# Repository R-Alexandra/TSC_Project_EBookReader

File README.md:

# TSC_Project_EBookReader - Rădulescu Alexandra

Acest proiect reprezintă un sistem de tip **eBook Reader** bazat pe microcontrolerul **ESP32-C6**, ce integrează module de stocare, afișare, senzori de mediu, alimentare prin baterie și interfețe de conectivitate. Dispozitivul este proiectat pentru un consum energetic scăzut și este compatibil cu multiple tipuri de afișaje E-Ink.

---
## Diagramă Bloc

---

## Bill of Materials (BOM)

| Componentă                | Link Achiziționare | Link Datasheet |
|---------------------------|--------------------|----------------|
| 112A-TAAR-R03 ATTEND      | https://store.comet.srl.ro/Catalogue/Product/43497/ | https://www.snapeda.com/parts/112A-TAAR-R03/Attend/datasheet/ |
| Condensator C0402         | https://ro.mouser.com/c/passive-components/capacitors/ceramic-capacitors/?q=CC0402 | https://componentsearchengine.com/Datasheets/2/CC0402MRX5R5BB106.pdf |
| Condensator Tantalum      | https://ro.mouser.com/ProductDetail/KYOCERA-AVX/TAJW107M010RNJ?qs=Wtp%252Bf%2FAeVqIH8v1VxV%252B1Rg%3D%3D | https://ro.mouser.com/datasheet/2/40/TAJ-3165264.pdf |
| CHG_LED                   | https://ro.mouser.com/ProductDetail/Kingbright/KP-1608SURCK?qs=2JU0tDl2GZ3FuyEWfBV1%2Fg== | https://www.snapeda.com/parts/KP-1608SURCK/Kingbright/datasheet/ |
| USBLC6-2SC6Y              | https://ro.mouser.com/ProductDetail/STMicroelectronics/USBLC6-2SC6Y?qs=gNDSiZmRJS%2FOgDexvXkdow%3D%3D | https://ro.mouser.com/datasheet/2/389/usblc6_2sc6y-1852505.pdf |
| SD0805S020S1R0            | https://ro.mouser.com/ProductDetail/KYOCERA-AVX/SD0805S020S1R0?qs=jCA%252BPfw4LHbpkAoSnwrdjw%3D%3D | https://ro.mouser.com/datasheet/2/40/schottky-3165252.pdf |
| MBR0530                   | https://ro.mouser.com/ProductDetail/onsemi-Fairchild/MBR0530?qs=VOMQJJE%252BBNniwJKcE3T43Q== | https://ro.mouser.com/datasheet/2/308/MBR0530_D-1810985.pdf |
| PGB1010603MR              | https://www.digikey.com/en/products/detail/littelfuse-inc/PGB1010603MR/715755 | https://www.littelfuse.com/assetdocs/pulseguard-esd-suppressors-pgb1-datasheet?assetguid=8a337998-d54d-466b-be4e-dc5bcd1f9321 |
| Rezistență R0402         | https://ro.mouser.com/c/passive-components/resistors/smd-resistors-chip-resistors/?case%20code%20-%20in=0402 | https://www.yageo.com/upload/media/product/products/datasheet/rchip/PYu-RC_Group_51_RoHS_L_12.pdf |
| BME680                    | https://ro.mouser.com/ProductDetail/Bosch-Sensortec/BME688?qs=IS%252B4QmGtzzqQoVDscqwx3A%3D%3D | https://ro.mouser.com/datasheet/2/783/bst_bme688_fl000-2307034.pdf |
| W25Q512JVEIQ              | https://ro.mouser.com/ProductDetail/Winbond/W25Q512JVEIQ?qs=l7cgNqFNU1jw6svr3at6tA%3D%3D | https://ro.mouser.com/datasheet/2/949/Winbond_W25Q512JV_Datasheet-3240039.pdf |
| ESP32-C6-WROOM-1-N8       | https://ro.mouser.com/ProductDetail/Espressif-Systems/ESP32-C6-WROOM-1-N8?qs=8Wlm6%252BaMh8ST02Gmwp74cw%3D%3D | https://ro.mouser.com/datasheet/2/891/Espressif_ESP32_C6_WROOM_1__Datasheet_V0_1_PRELIMI-3239987.pdf |
| DS3231SN#                 | https://ro.mouser.com/ProductDetail/Analog-Devices-Maxim-Integrated/DS3231SN?qs=1eQvB6Dk1vhUlr8%2FOrV0Fw%3D%3D | https://ro.mouser.com/datasheet/2/609/DS3231-3421123.pdf |
| MAX17048G+T10             | https://ro.mouser.com/ProductDetail/Analog-Devices-Maxim-Integrated/MAX17048G%2bT10?qs=D7PJwyCwLAoGnnn8jEPRBQ%3D%3D | https://ro.mouser.com/datasheet/2/609/MAX17048_MAX17049-3469099.pdf |
| MCP73831                  | https://ro.mouser.com/ProductDetail/Microchip-Technology/MCP73831T-2ATI-OT?qs=yUQqVecv4qsZbioEUu%252B83g%3D%3D | https://ro.mouser.com/datasheet/2/268/MCP73831_Family_Data_Sheet_DS20001984H-3441711.pdf |
| BD5229G-TR                | https://www.digikey.com/en/products/detail/rohm-semiconductor/BD5229G-TR/3663792 | https://fscdn.rohm.com/en/products/databook/datasheet/ic/power/voltage_detector/bd52xxg-e.pdf |
| XC6220A331MR-G            | https://ro.mouser.com/ProductDetail/Torex-Semiconductor/XC6220A331MR-G?qs=AsjdqWjXhJ8ZSWznL1J0gg%3D%3D | https://ro.mouser.com/datasheet/2/760/xc6220-3371556.pdf |
| FH34SRJ-24S-0.5SH(99)     | https://ro.mouser.com/ProductDetail/Hirose-Connector/FH34SRJ-24S-0.5SH99?qs=vcbW%252B4%252BSTIpKBl5ap9J8Fw%3D%3D | https://ro.mouser.com/datasheet/2/185/FH34SRJ_24S_0_5SH_99__CL0580_1255_6_99_2DDrawing_0-1615044.pdf |
| USB4110-GF-A              | https://ro.mouser.com/ProductDetail/GCT/USB4110-GF-A?qs=KUoIvG%2F9IlYiZvIXQjyJeA%3D%3D | https://ro.mouser.com/datasheet/2/837/GCT_USB4110_Product_Drawing___20k_cycles-3455479.pdf |
| QWIIC_RIGHT_ANGLE         | https://ro.mouser.com/ProductDetail/SparkFun/PRT-14417?qs=wd5RIQLrsJhgdz%2FpmZ%2F3GQ== | https://ro.mouser.com/datasheet/2/813/Qwiic_Connector_Datasheet-1223982.pdf |
| Bobină 744043680         | https://ro.mouser.com/ProductDetail/Wurth-Elektronik/744043680?qs=PGXP4M47uW6VkZq%252BkzjrHA%3D%3D | https://www.we-online.com/components/products/datasheet/744043680.pdf |
| PFMF.050.1                | https://ro.mouser.com/ProductDetail/EPCOS-TDK/B72520T0350K062?qs=dEfas%2FXlABIszF52uu7vrg%3D%3D | https://www.tdk-electronics.tdk.com/inf/75/db/CTVS_14/Surge_protection_series.pdf |
| DMG2305UX-7               | https://www.digikey.com/en/products/detail/diodes-incorporated/DMG2305UX-7/4340666 | https://www.diodes.com/assets/Datasheets/DMG2305UX.pdf |
| Si1308EDL-T1-GE3          | https://www.digikey.com/en/products/detail/vishay-siliconix/SI1308EDL-T1-GE3/4876435 | https://www.vishay.com/docs/63399/si1308edl.pdf |
| Solder Jumper (SJ)        | https://grabcad.com/library/solder-jumpers-1 | https://grabcad.com/library/solder-jumpers-1 |
| Buton                     | https://industry.panasonic.com/global/en/products/control/switch/light-touch/number/evqpuj02k | https://industry.panasonic.com/global/en/downloads?tab=catalog&small_g_cd=203&part_no=EVQPUJ02K |
| CPH3225A                  | https://www.digikey.com/en/products/detail/seiko-instruments/CPH3225A/8692444 | https://mm.digikey.com/Volume0/opasdata/d220001/medias/docus/6537/rev05-CPHCPM.pdf |

---

## Descriere a componentelor și funcționalității hardware

### Microcontroller: ESP32-C6

- Microcontroller RISC-V pe 32 de biți cu suport **Wi-Fi 6** și **Bluetooth 5 Low Energy (BLE)**
- Alimentat la **3.3V**
- Gestionează toate perifericele proiectului
- Oferă multiple interfețe  **GPIO, SPI, I2C, UART**
  - **SPI**(Serial Peripheral Interface): pentru conectare la memoria NOR Flash, cardul SD și afișajul E-Ink
  - **I2C**(Inter-Integrated Circuit): pentru conectare la senzorul BME688, modulul RTC DS3231 și senzorul de nivel baterie MAX17048
  - **GPIO**(General Purpose Input/Output): utilizat pentru semnale de control pentru ecranul E-Ink, butoane și detecție SD
- Are o arhitectură optimizată pentru **consum redus de energie**, ideală pentru aplicații portabile

### Alimentare și protecție

#### Regulator de tensiune LDO

- **XC6206P332MR-G** transformă tensiunea VIN (5V) în 3.3V și  este folosit un tranzistor suplimentar pentru controlul alimentării

#### Controller de încărcare baterie

- **MCP73831** gestionează încărcarea bateriei Li-Po 3.7V cu protecție integrată contra supratensiunii și a curentului excesiv
- LED-uri pentru semnalizare stare de încărcare

#### Monitorizare nivel baterie

- **MAX17048** oferă monitorizare în timp real a stării de încărcare a bateriei 
- Comunică cu ESP32-C6 prin interfața I2C

#### Conector USB-C și protecție ESD

- Conector **USB-C** pentru alimentare și comunicație
- Protecție la descărcări electrostatice realizată prin **PMF0501** și **USBLC6-2SC6Y**, care protejează liniile de alimentare și semnal

## Stocare

### Card microSD

- Conectat la magistrala **SPI**
- Permite stocarea fișierelor eBook și a jurnalelor de sistem
- Linie dedicată pentru **detectare automată** a cardului

### Memorie NOR Flash externă (64MB)

- Chipul **W25Q512JVEIQ** furnizeză memorie nevolatilă pentru firmware și resurse statice
- Conectată la magistrala **SPI**

## Afișaj E-Paper

### Interfață EPD dedicată

- Include toate conexiunile necesare pentru controlul unui ecran E-Ink (**SPI**, semnale de control precum **EPD_BUSY, EPD_DC, EPD_RST** etc).
- Header dedicat EPD cu 20 pini, compatibil cu mai multe modele DE afișaje.

### Circuit de alimentare EPD

- Utilizează un convertor DC-DC și tranzistoare MOSFET pentru a genera tensiunile de alimentare cerute de ecranele E-Ink.

### Selector tip afișaj

- Permite alegerea tipului de ecran conectat, în funcție de compatibilitatea cu semnalele de control.

## Senzor BME680

- Măsoară: **temperatură, umiditate, presiune atmosferică, calitate aer (VOCs)**
- Este conectat prin interfața **I2C** (SDA și SCL)

## Modul RTC (DS3231SN)

- Precizie ridicată pentru a păstra ora și data corectă, chiar și în absența alimentării principale.
- Interfață **I2C** (SDA și SCL)

## Butoane de control

- Buton **RESET**
- Buton **BOOT**
- Buton custom **IO/CHANGE**

## Test Pads și Conectori de extensie

- Sunt prezente **paduri de testare** și debugging 
- Conector **Qwiic/Stemma QT** pentru extinderea rapidă a sistemului cu senzori I2C suplimentari

## Protecție ESD pentru SPI

- Liniile **SPI** sunt protejate împotriva descărcărilor electrostatice

---

## Consum estimativ de energie
Sistemul este proiectat pentru un consum energetic redus, aspect esențial pentru funcționarea pe baterie.

| Componentă               | Consum estimativ       |
|--------------------------|-------------------------|
| ESP32-C6 (Wi-Fi activ)   | 120 – 150 mA            |
| Afișaj EPD               | 20 – 40 mA              |
| Senzor BME688            | 1 – 2 mA                |
| Card SD (scriere/citire)| 50 – 100 mA             |
| MAX17048 + RTC DS3231    | < 1 mA                  |
| **Total (mod activ)**    | **~300 mA**             |
| **Total (deep sleep)**   | **< 10 mA**             |

### Estimare autonomie (baterie LiPo 2000mAh):
- **Folosire intensivă**: câteva ore
- **Standby cu afiș static**: zile/săptămâni

---

## Alocarea pinilor ESP32-C6

### 1. Afișaj EPD (e-paper display)

| Pin ESP32-C6 | Funcție     | Observație                          |
|--------------|-------------|--------------------------------------|
| IO3 (26)     | EPD_BUSY    | Verifică dacă ecranul este ocupat   |
| IO5 (5)      | EPD_DC      | Comută între date și comandă        |
| IO6 (6)      | SCK         | Linie de ceas SPI                   |
| IO7 (7)      | MOSI        | Transmisie date SPI                 |
| IO10 (11)    | EPD_CS      | Selectare chip pentru EPD           |
| IO23 (21)    | EPD_RST     | Resetare ecran                      |
| IO20 (18)    | EPD_3V3_C   | Control alimentare 3V3 pentru EPD   |

### 2. Card SD

| Pin ESP32-C6 | Funcție     | Observație                          |
|--------------|-------------|--------------------------------------|
| IO2 (27)     | MISO        | Recepție date SPI                   |
| IO4 (4)      | SS_SD       | Selectare chip SD                   |
| IO6 (6)      | SCK         | Linie de ceas SPI                   |
| IO7 (7)      | MOSI        | Transmisie date SPI                 |

### 3. Memorie Flash NOR

| Pin ESP32-C6 | Funcție     | Observație                          |
|--------------|-------------|--------------------------------------|
| IO11 (12)    | FLASH_CS    | Selectare chip Flash                |
| IO2 (27)     | MISO        | Recepție date SPI                   |
| IO6 (6)      | SCK         | Linie de ceas SPI                   |
| IO7 (7)      | MOSI        | Transmisie date SPI                 |

### 4. Magistrală I2C (BME688, RTC DS3231, MAX17048)

| Pin ESP32-C6 | Funcție     | Observație                          |
|--------------|-------------|--------------------------------------|
| IO21 (19)    | SDA         | Linie de date I2C                   |
| IO22 (20)    | SCL         | Linie de ceas I2C                   |
| IO19 (17)    | I2C_PW      | Activare alimentare senzori I2C     |

### 5. RTC (DS3231)

| Pin ESP32-C6 | Funcție     | Observație                          |
|--------------|-------------|--------------------------------------|
| IO0 (8)      | INT_RTC     | Semnal de întrerupere               |
| IO1 (9)      | 32KHz       | Ieșire ceas precis                  |
| IO18 (16)    | RTC_RST     | Reset hardware RTC                  |

### 6. Conectivitate USB

| Pin ESP32-C6 | Funcție     | Observație                          |
|--------------|-------------|--------------------------------------|
| IO12 (13)    | USB_D-      | Comunicație USB                     |
| IO13 (14)    | USB_D+      | Comunicație USB                     |

### 7. Serială UART 

| Pin ESP32-C6 | Funcție     | Observație                          |
|--------------|-------------|--------------------------------------|
| IO16 (25)    | TX          | Transmisie UART                     |
| IO17 (24)    | RX          | Recepție UART                       |

### 8. Butoane 

| Pin ESP32-C6 | Funcție     | Observație                          |
|--------------|-------------|--------------------------------------|
| EN (3)       | RESET       | Reset general microcontroler        |
| IO8 (10)     | IO/BOOT     | Buton BOOT (pus pe GND la pornire)  |
| IO15 (23)    | IO/CHANGE   | Buton custom                        |

### 9. Alimentare și Referință

| Pin ESP32-C6 | Funcție     | Observație                          |
|--------------|-------------|--------------------------------------|
| Pin 2        | 3V3         | Alimentare principală               |
| Pin 1        | GND         | Împământare                         |

---

## Considerații privind realizarea proiectului
În procesul de realizare a designului hardware am respectat cerințele din ghidurile de proiectare (ERC, DRC, layout) și am încercat să iau decizii care să ofere echilibru între funcționalitate, integrare și respectarea bunelor practici. Amplasarea componentelor am făcut-o atât pe baza documentației oferite (dimensiuni mecanice și recomandări de placement), cât și pentru o rutare cât mai bună, care să reducă interferențele și să faciliteze traseele de alimentare și semnal.

Pentru designul PCB-ului, am folosit DRC-ul oferit pentru verificare și am rezolvat erorile apărute, inclusiv prin ajustarea dimensiunii unor footprint-uri. Am aplicat regulile de rutare pentru traseele de putere și pentru date, evitând unghiurile drepte. Traseele de alimentare au lățimea de 0.3mm, restul traseelor de 0.15mm și am realizat câte un plan de masă atât pentru top cât și pe bottom. Test pad-urile rămase le-am poziționat astfel încât să putem testa rapid anumite componente: 
- lângă header-ul display-ului pentru a testa alimentarea și semnalele de date către ecran;
- lângă ESP32-C6 pentru a verifica semnale critice și pentru debugging.

Am avut în vedere și integrarea finală în ansamblul 3D al carcasei. De aceea, am poziționat conectorii astfel încât să fie accesibili din exterior, iar unele componente au fost ușor translatate pentru a obține o potrivire corectă și o funcționare bună a dispozitivului. De asemenea, am desenat bateria și ecranul folosind dimensiunile mecanice specificate pentru o integrare cât mai bună.

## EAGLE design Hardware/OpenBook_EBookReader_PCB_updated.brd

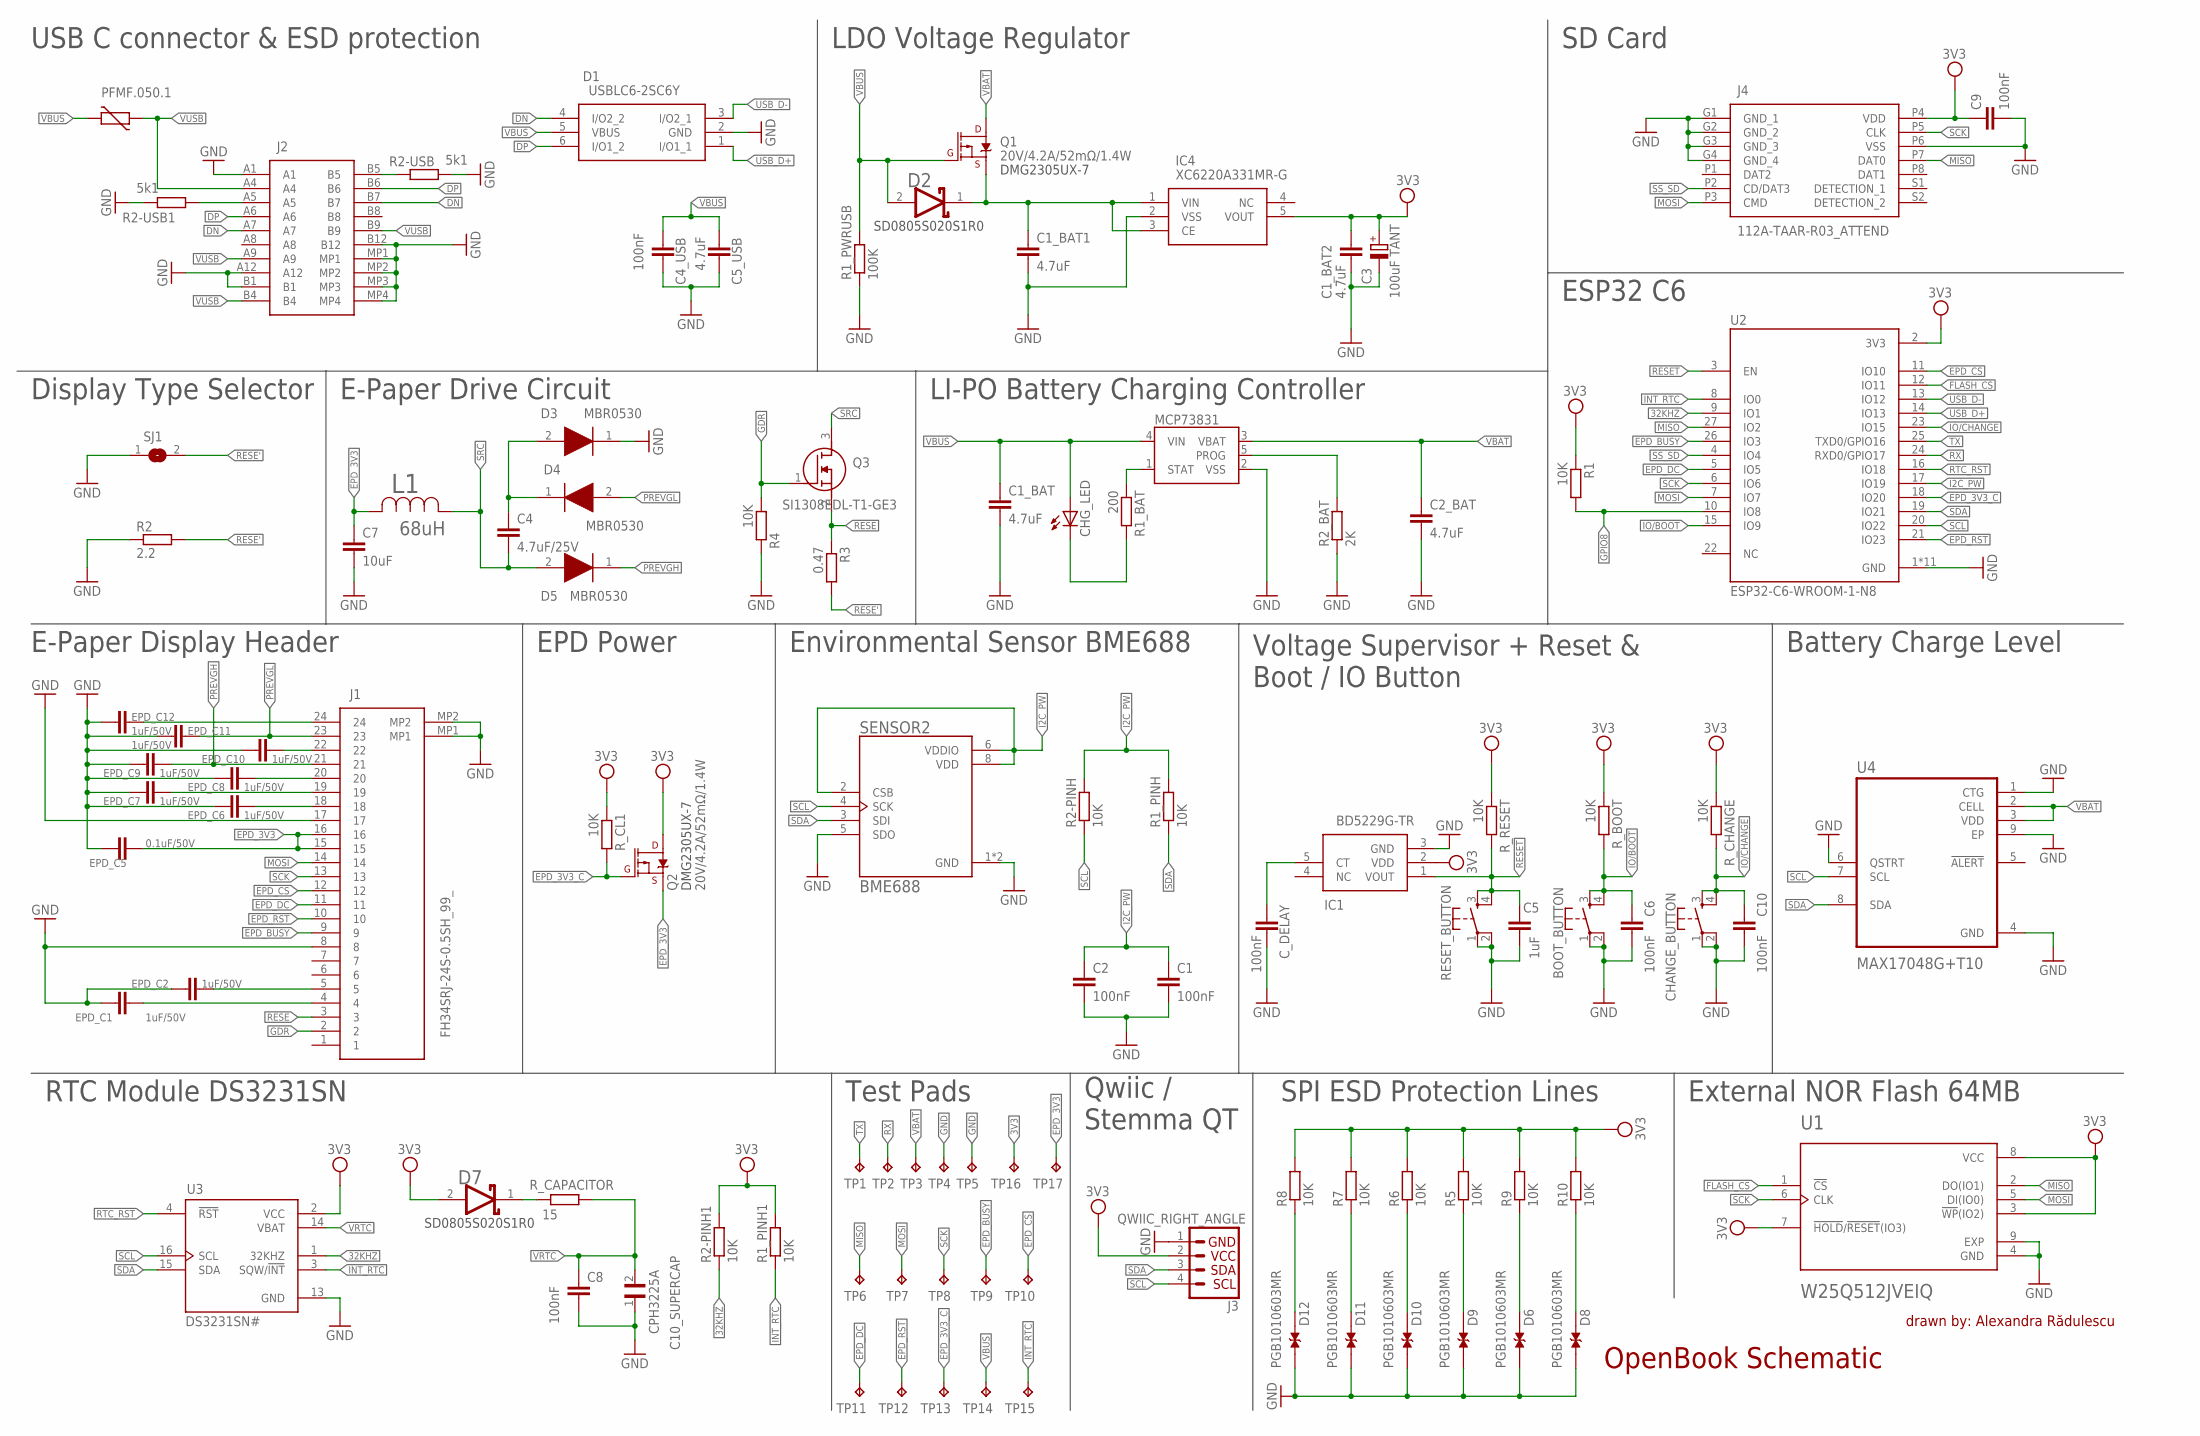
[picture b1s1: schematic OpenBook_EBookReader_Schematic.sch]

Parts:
BOOT_BUTTON: BUTTON_CUSYOMV1; MYBUTTON
C1, C2, C4_USB, C6, C8, C9, C10: 100nF; ESP32_WROVER_EAGLE-LTSPICE_C0402
C1_BAT, C1_BAT1, C1_BAT2, C2_BAT, C5_USB: 4.7uF; ESP32_WROVER_EAGLE-LTSPICE_C0402
C3: 100uF TANT; RCL_CT3528
C4: 4.7uF/25V; ESP32_WROVER_EAGLE-LTSPICE_C0402
C5: 1uF; ESP32_WROVER_EAGLE-LTSPICE_C0402
C7: 10uF; ESP32_WROVER_EAGLE-LTSPICE_C0402
C10_SUPERCAP: CPH3225A; CAPCP3225X100N
CHANGE_BUTTON: BUTTON_CUSYOMV1; MYBUTTON
CHG_LED: ADAFRUIT_LEDCHIP-LED0603; ADAFRUIT_CHIP-LED0603
C_DELAY: 100nF; ESP32_WROVER_EAGLE-LTSPICE_C0402
D1: USBLC6-2SC6Y; SOT95P280X145-6N
D2: ESP32_WROVER_AVX---SD0805S020S1R0_AVX_SD0805S020S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; ESP32_WROVER_AVX---SD0805S020S1R0_AVX_SD0805S020S1R0_0
D3, D4, D5: MBR0530; SOD3716X135N
D6, D8, D9, D10, D11, D12: PGB1010603MR; DIOC1608X36N
D7: SD0805S020S1R0; ESP32_WROVER_AVX---SD0805S020S1R0_AVX_SD0805S020S1R0_0
EPD_C1, EPD_C2, EPD_C6, EPD_C7, EPD_C8, EPD_C9, EPD_C10, EPD_C11, EPD_C12: 1uF/50V; ESP32_WROVER_EAGLE-LTSPICE_C0402
EPD_C5: 0.1uF/50V; ESP32_WROVER_EAGLE-LTSPICE_C0402
IC1: BD5229G-TR; SOT95P280X125-5N
IC4: XC6220A331MR-G; SOT95P280X120-5N
J1: FH34SRJ-24S-0.5SH_99_; FH34SRJ24S05SH99
J2: SAMACSYS_PARTS_USB4110-GF-A; SAMACSYS_PARTS_USB4110GFA
J3: QWIIC_RIGHT_ANGLE; JST04_1MM_RA
J4: 112A-TAAR-R03_ATTEND; 112ATAARR03ATTEND
L1: 68uH; IND_4828-WE-TPC_WRE
MCP73831: ESP32_WROVER_SPARKFUN-IC-POWER_MCP73831; ESP32_WROVER_SPARKFUN-IC-POWER_SOT23-5
PFMF.050.1: ESP32C6_VARISTORCN1812; ESP32C6_VARISTOR_CT/CN1812
Q1, Q2: 20V/4.2A/52mΩ/1.4W; ESP32_WROVER_SPARKFUN-DISCRETESEMI_SOT23-3
Q3: SI1308EDL-T1-GE3; SOT65P210X110-3N
R1, R1_PINH, R1_PINH1, R2-PINH, R2-PINH1, R4, R5, R6, R7, R8, R9, R10: 10K; ESP32_WROVER_EAGLE-LTSPICE_R0402
R1_BAT: 200; ESP32_WROVER_EAGLE-LTSPICE_R0402
R1_PWRUSB: 100K; ESP32_WROVER_EAGLE-LTSPICE_R0402
R2: 2.2; ESP32_WROVER_EAGLE-LTSPICE_R0402
R2-USB, R2-USB1: 5k1; ESP32_WROVER_EAGLE-LTSPICE_R0402
R2_BAT: 2K; ESP32_WROVER_EAGLE-LTSPICE_R0402
R3: 0.47; ESP32_WROVER_EAGLE-LTSPICE_R0402
RESET_BUTTON: BUTTON_CUSYOMV1; MYBUTTON
R_BOOT: 10K; ESP32_WROVER_EAGLE-LTSPICE_R0402
R_CAPACITOR: 15; ESP32_WROVER_EAGLE-LTSPICE_R0402
R_CHANGE: 10K; ESP32_WROVER_EAGLE-LTSPICE_R0402
R_CL1: 10K; ESP32_WROVER_EAGLE-LTSPICE_R0402
R_RESET: 10K; ESP32_WROVER_EAGLE-LTSPICE_R0402
SENSOR2: BME688; ESP32_WROVER_BME680_PSON80P300X300X100-8N
SJ1: SJ
TP1, TP2, TP3, TP4, TP5, TP6, TP7, TP8, TP9, TP10, TP11, TP12, TP13, TP14, TP15, TP16, TP17: TPTP20R; TP20R
U1: W25Q512JVEIQ; SON127P600X800X80-9N
U2: ESP32-C6-WROOM-1-N8; XCVR_ESP32-C6-WROOM-1-N8
U3: DS3231SN#; SOIC127P1032X265-16N
U4: MAX17048G+T10; SON50P200X200X80-9N

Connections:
3V3: C1_BAT2.1, C3.+, C9.1, D7.2 (ANODE), IC1.2 (VDD), IC4.5 (VOUT), J3.2, J4.P4 (VDD), Q2.3 (D), R1.1, R1_PINH1.2, R2-PINH1.2, R5.2, R6.2, R7.2, R8.2, R9.2, R10.2, R_BOOT.1, R_CHANGE.1, R_CL1.1, R_RESET.1, TP16.TP, U1.3 (!WP!(IO2)), U1.7 (!HOLD!/!RESET!(IO3)), U1.8 (VCC), U2.2 (3V3), U3.2 (VCC)
32KHZ: R2-PINH1.1, U2.9 (IO1), U3.1 (32KHZ)
DN: D1.4 (I/O2_2), J2.A7, J2.B7
DP: D1.6 (I/O1_2), J2.A6, J2.B6
EPD_3V3: C7.1, EPD_C5.1, J1.15, J1.16, L1.2, Q2.2 (S), TP17.TP
EPD_3V3_C: Q2.1 (G), R_CL1.2, TP13.TP, U2.18 (IO20)
EPD_BUSY: J1.9, TP9.TP, U2.26 (IO3)
EPD_CS: J1.12, TP10.TP, U2.11 (IO10)
EPD_DC: J1.11, TP11.TP, U2.5 (IO5)
EPD_RST: J1.10, TP12.TP, U2.21 (IO23)
FLASH_CS: U1.1 (!CS), U2.12 (IO11)
GDR: J1.2, Q3.1 (G), R4.1
GND: BOOT_BUTTON.1, BOOT_BUTTON.2, C1.2, C1_BAT.2, C1_BAT1.2, C1_BAT2.2, C2.2, C2_BAT.2, C3.-, C4_USB.2, C5.2, C5_USB.2, C6.2, C7.2, C8.2, C9.2, C10.2, C10_SUPERCAP.1, CHANGE_BUTTON.1, CHANGE_BUTTON.2, C_DELAY.2, D1.2 (GND), D3.1 (K), D6.1, D8.1, D9.1, D10.1, D11.1, D12.1, EPD_C1.2, EPD_C2.2, EPD_C5.2, EPD_C6.2, EPD_C7.2, EPD_C8.2, EPD_C9.2, EPD_C10.2, EPD_C11.2, EPD_C12.2, IC1.3 (GND), IC4.2 (VSS), J1.8, J1.17, J1.MP1, J1.MP2, J2.A1, J2.A12, J2.B1, J2.B12, J2.MP1, J2.MP2, J2.MP3, J2.MP4, J3.1, J4.G1 (GND_1), J4.G2 (GND_2), J4.G3 (GND_3), J4.G4 (GND_4), J4.P6 (VSS), MCP73831.2 (VSS), R1_PWRUSB.1, R2.1, R2-USB.2, R2-USB1.1, R2_BAT.1, R4.2, RESET_BUTTON.1, RESET_BUTTON.2, SENSOR2.1 (GND), SENSOR2.5 (SDO), SENSOR2.7 (GND), SJ1.1, TP4.TP, TP5.TP, U1.4 (GND), U1.9 (EXP), U2.1 (GND), U2.28 (GND), U2.29_1 (GND), U2.29_2 (GND), U2.29_3 (GND), U2.29_4 (GND), U2.29_5 (GND), U2.29_6 (GND), U2.29_7 (GND), U2.29_8 (GND), U2.29_9 (GND), U3.13 (GND), U4.1 (CTG), U4.4 (GND), U4.6 (QSTRT), U4.9 (EP)
GPIO8: R1.2, U2.10 (IO8)
I2C_PW: C1.1, C2.1, R1_PINH.2, R2-PINH.2, SENSOR2.2 (CSB), SENSOR2.6 (VDDIO), SENSOR2.8 (VDD), U2.17 (IO19)
INT_RTC: R1_PINH1.1, TP15.TP, U2.8 (IO0), U3.3 (SQW/!INT)
IO/BOOT: BOOT_BUTTON.3, BOOT_BUTTON.4, C6.1, R_BOOT.2, U2.15 (IO9)
IO/CHANGE: C10.1, CHANGE_BUTTON.3, CHANGE_BUTTON.4, R_CHANGE.2, U2.23 (IO15)
MISO: J4.P7 (DAT0), TP6.TP, U1.2 (DO(IO1)), U2.27 (IO2)
MOSI: J1.14, J4.P3 (CMD), TP7.TP, U1.5 (DI(IO0)), U2.7 (IO7)
unnamed: C1_BAT1.1, D2.1 (CATHODE), IC4.1 (VIN), IC4.3 (CE), Q1.2 (S)
unnamed: CHG_LED.C, R1_BAT.2
unnamed: MCP73831.1 (STAT), R1_BAT.1
unnamed: EPD_C12.1, J1.24
unnamed: C4.1, D3.2 (A), D4.1 (K)
unnamed: J2.B5, R2-USB.1
unnamed: MCP73831.5 (PROG), R2_BAT.2
unnamed: C_DELAY.1, IC1.5 (CT)
unnamed: EPD_C10.1, J1.22
unnamed: J2.A5, R2-USB1.2
unnamed: D7.1 (CATHODE), R_CAPACITOR.2
unnamed: EPD_C8.1, J1.20
unnamed: EPD_C7.1, J1.19
unnamed: EPD_C6.1, J1.18
unnamed: D12.2, R8.1
unnamed: D11.2, R7.1
unnamed: D10.2, R6.1
unnamed: D9.2, R5.1
unnamed: D6.2, R9.1
unnamed: D8.2, R10.1
unnamed: EPD_C2.1, J1.5
unnamed: EPD_C1.1, J1.4
PREVGH: D5.1 (K), EPD_C9.1, J1.21
PREVGL: D4.2 (A), EPD_C11.1, J1.23
RESE: J1.3, Q3.2 (S), R3.1
RESE': R2.2, R3.2, SJ1.2
RESET: C5.1, IC1.1 (VOUT), RESET_BUTTON.3, RESET_BUTTON.4, R_RESET.2, U2.3 (EN)
RTC_RST: U2.16 (IO18), U3.4 (!RST)
RX: TP2.TP, U2.24 (RXD0/GPIO17)
SCK: J1.13, J4.P5 (CLK), TP8.TP, U1.6 (CLK), U2.6 (IO6)
SCL: J3.4, R2-PINH.1, SENSOR2.4 (SCK), U2.20 (IO22), U3.16 (SCL), U4.7 (SCL)
SDA: J3.3, R1_PINH.1, SENSOR2.3 (SDI), U2.19 (IO21), U3.15 (SDA), U4.8 (SDA)
SRC: C4.2, D5.2 (A), L1.1, Q3.3 (D)
SS_SD: J4.P2 (CD/DAT3), U2.4 (IO4)
TX: TP1.TP, U2.25 (TXD0/GPIO16)
USB_D+: D1.1 (I/O1_1), U2.14 (IO13)
USB_D-: D1.3 (I/O2_1), U2.13 (IO12)
VBAT: C2_BAT.1, MCP73831.3 (VBAT), Q1.3 (D), TP3.TP, U4.2 (CELL), U4.3 (VDD)
VBUS: C1_BAT.1, C4_USB.1, C5_USB.1, CHG_LED.A, D1.5 (VBUS), D2.2 (ANODE), MCP73831.4 (VIN), PFMF.050.1.2, Q1.1 (G), R1_PWRUSB.2, TP14.TP
VRTC: C8.1, C10_SUPERCAP.2, R_CAPACITOR.1, U3.14 (VBAT)
VUSB: J2.A4, J2.A9, J2.B4, J2.B9, PFMF.050.1.1

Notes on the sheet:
USB C connector & ESD protection
Display Type Selector
LDO Voltage Regulator
DMG2305UX-7
SD Card
ESP32 C6
Battery Charge Level
E-Paper Drive Circuit
LI-PO Battery Charging Controller
E-Paper Display Header
EPD Power
Environmental Sensor BME688
Voltage Supervisor + Reset & Boot / IO Button
RTC Module DS3231SN
Test Pads
Qwiic / Stemma QT
SPI ESD Protection Lines
External NOR Flash 64MB
SD0805S020S1R0
OpenBook Schematic
drawn by: Alexandra Rădulescu

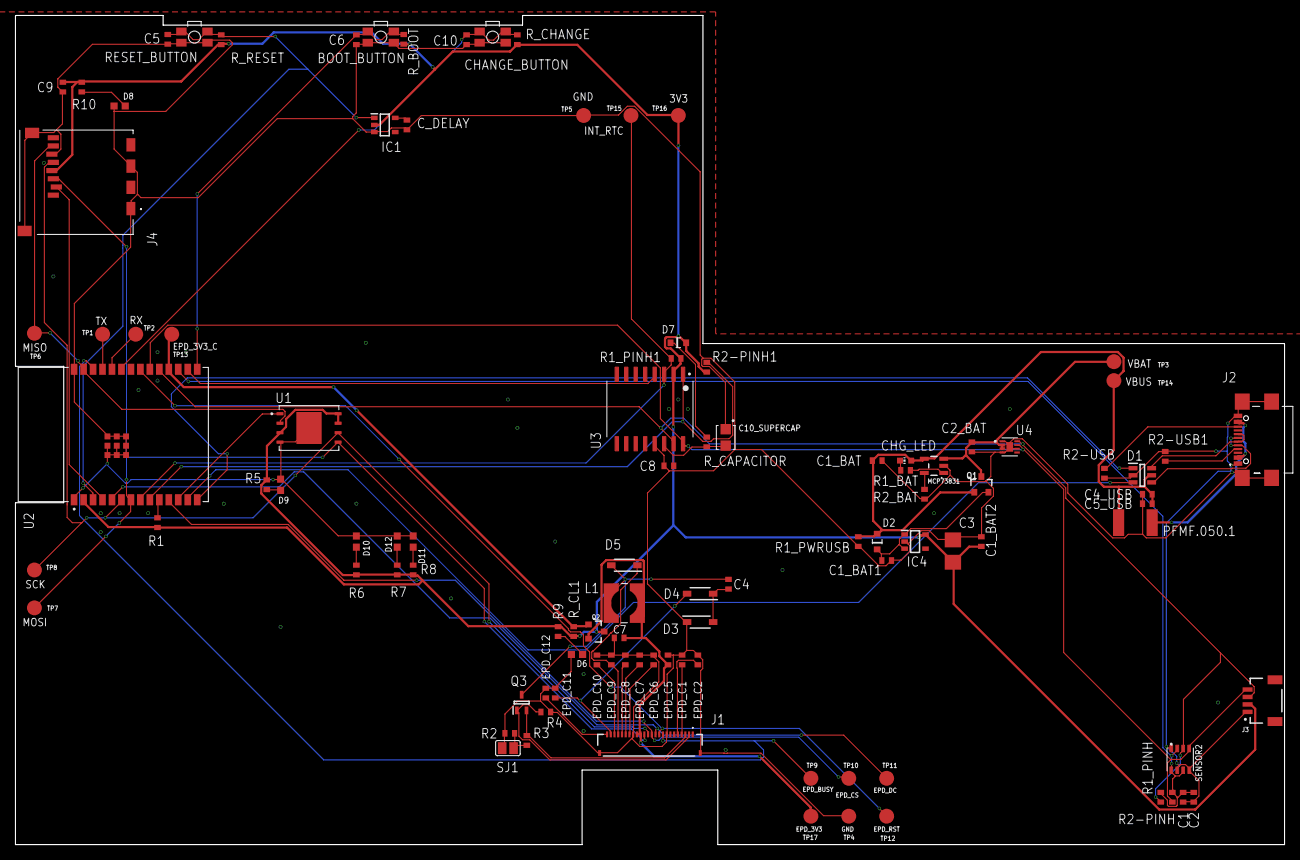
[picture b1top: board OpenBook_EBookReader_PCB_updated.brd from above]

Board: 2 copper layers, 170.2 x 111.2 mm, 103 parts (0 on the bottom side), 61 nets.

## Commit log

2025-04-06 LICENSE
2025-04-06 Hardware Upload
2025-04-06 Manufacturing Upload
2025-04-06 Mechanical Upload
2025-04-06 Images Upload
2025-04-13 Update Hardware
2025-04-13 Update Mechanical
2025-04-13 Update Images
2025-04-15 Update Manufacturing

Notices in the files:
parts and their libraries:
COPYRIGHT: Copyright (C) 2024 Ultra Librarian. All rights reserved.
